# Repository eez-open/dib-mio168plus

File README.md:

### This is a WORK IN PROGRESS!

---

### Ownership and License
The contributors are listed in CONTRIB.TXT. 

Licenses | OSHWA UID
--|--
 | 

### Overview

_Fig 1: MIO168+ without AFE module_

_Fig 2: MIO168+ with AFE3+ installed_

The MIO168+ module features multiple digital I/O, analog outputs and expansion connectors for carry various AFEs.

### Feature list

* On-board [STM32F446ZCT6](https://www.st.com/content/st_com/en/products/microcontrollers-microprocessors/stm32-32-bit-arm-cortex-mcus/stm32-high-performance-mcus/stm32f4-series/stm32f446/stm32f446zc.html) high-performance foundation line MCU, ARM Cortex-M4 with DSP and FPU, 256 KiB Flash, LQFP-144 package 
* AFE interface
* 8 x protected digital inputs (3.3/5/24 V), 2 x fast/slow, 6 x slow
* 8 x digital outputs with multiple protections, voltage clamp 24V, nom. current 330 mA (limit 2.3 A)
* 2 x PWM outputs (protected) or sensor bias power (+/-15 V, max. 10 mA)
* 2 x analog bipolar outputs (+/-5 V, +/-10 V, 0-5 V, 0-10 V). Voltage or current output with protection. 12-bit DAC, replaceable with pin compatible 14- or 16-bit version
* 2 x analog bipolar outputs +/-10 V. 12-bit DAC, replaceable with pin compatible 14- or 16-bit version
* On-board isolated power supply with +/-5.3 V outputs (with 4x multipliers), +/-15 V and +3.3 V LDO
* On-board SDRAM for measured data buffering (optional)
* USB HS PHY
* Firmware download via SPI or USB
* Optional SWD for debugging
* I2C EEPROM for storing board specific parameters
* Dimensions: 180 x 95 mm, 4-layer PCB

### Related topics and links

* [EEZ BB3+](https://github.com/eez-open/eez-bb3plus)
* [MIO168+ AFE3](https://github.com/eez-open/dib-mio168plus-afe3)
* [MIO168](https://github.com/eez-open/dib-mio168) for EEZ BB3 (retired)

---

This work is financed by [NLnet](https://nlnet.nl/project/BB3-CM5/) foundation

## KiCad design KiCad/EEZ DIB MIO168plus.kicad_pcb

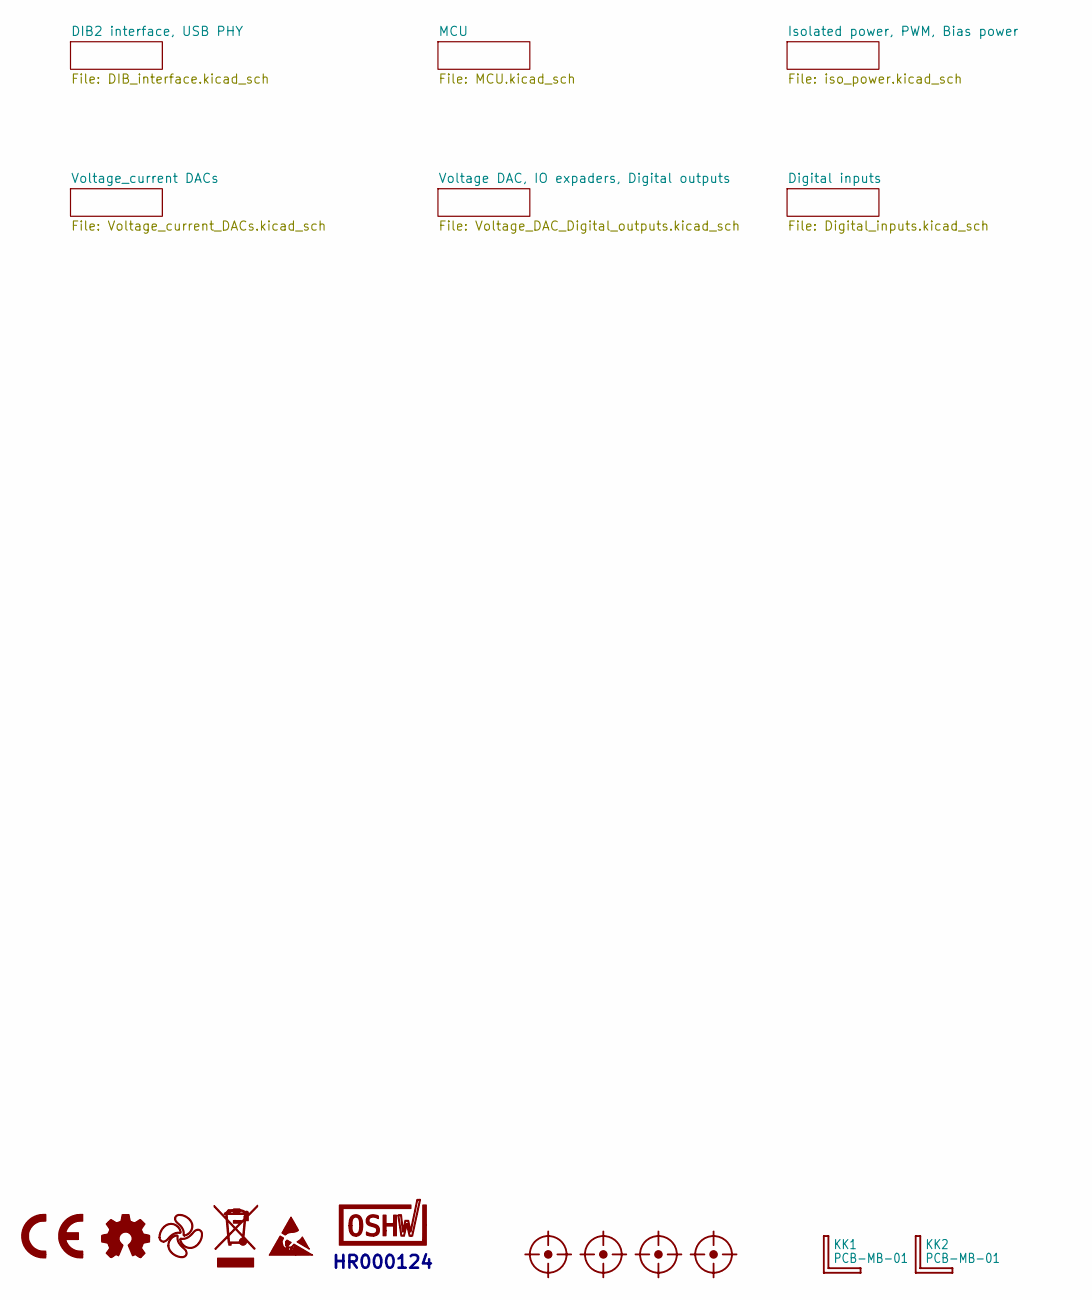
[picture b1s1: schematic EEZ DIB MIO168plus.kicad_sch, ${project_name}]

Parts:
FM1, FM2, FM3, FM4: FIDUCIAL_2; Fiducial_0.75mm_Mask1.5mm
KK1, KK2: PCB-MB-01; DigiKey RPC1760-ND
LOGO1: CE logo
LOGO2: Open hardware logo; Open HW logo
LOGO3: EEZ logo; EEZ logo (outline 6mm)
LOGO4: WEEE logo
LOGO5: ESD logo
LOGO6: OSHWA logo; OSHWA logo 6.6mm

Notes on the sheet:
HR000124

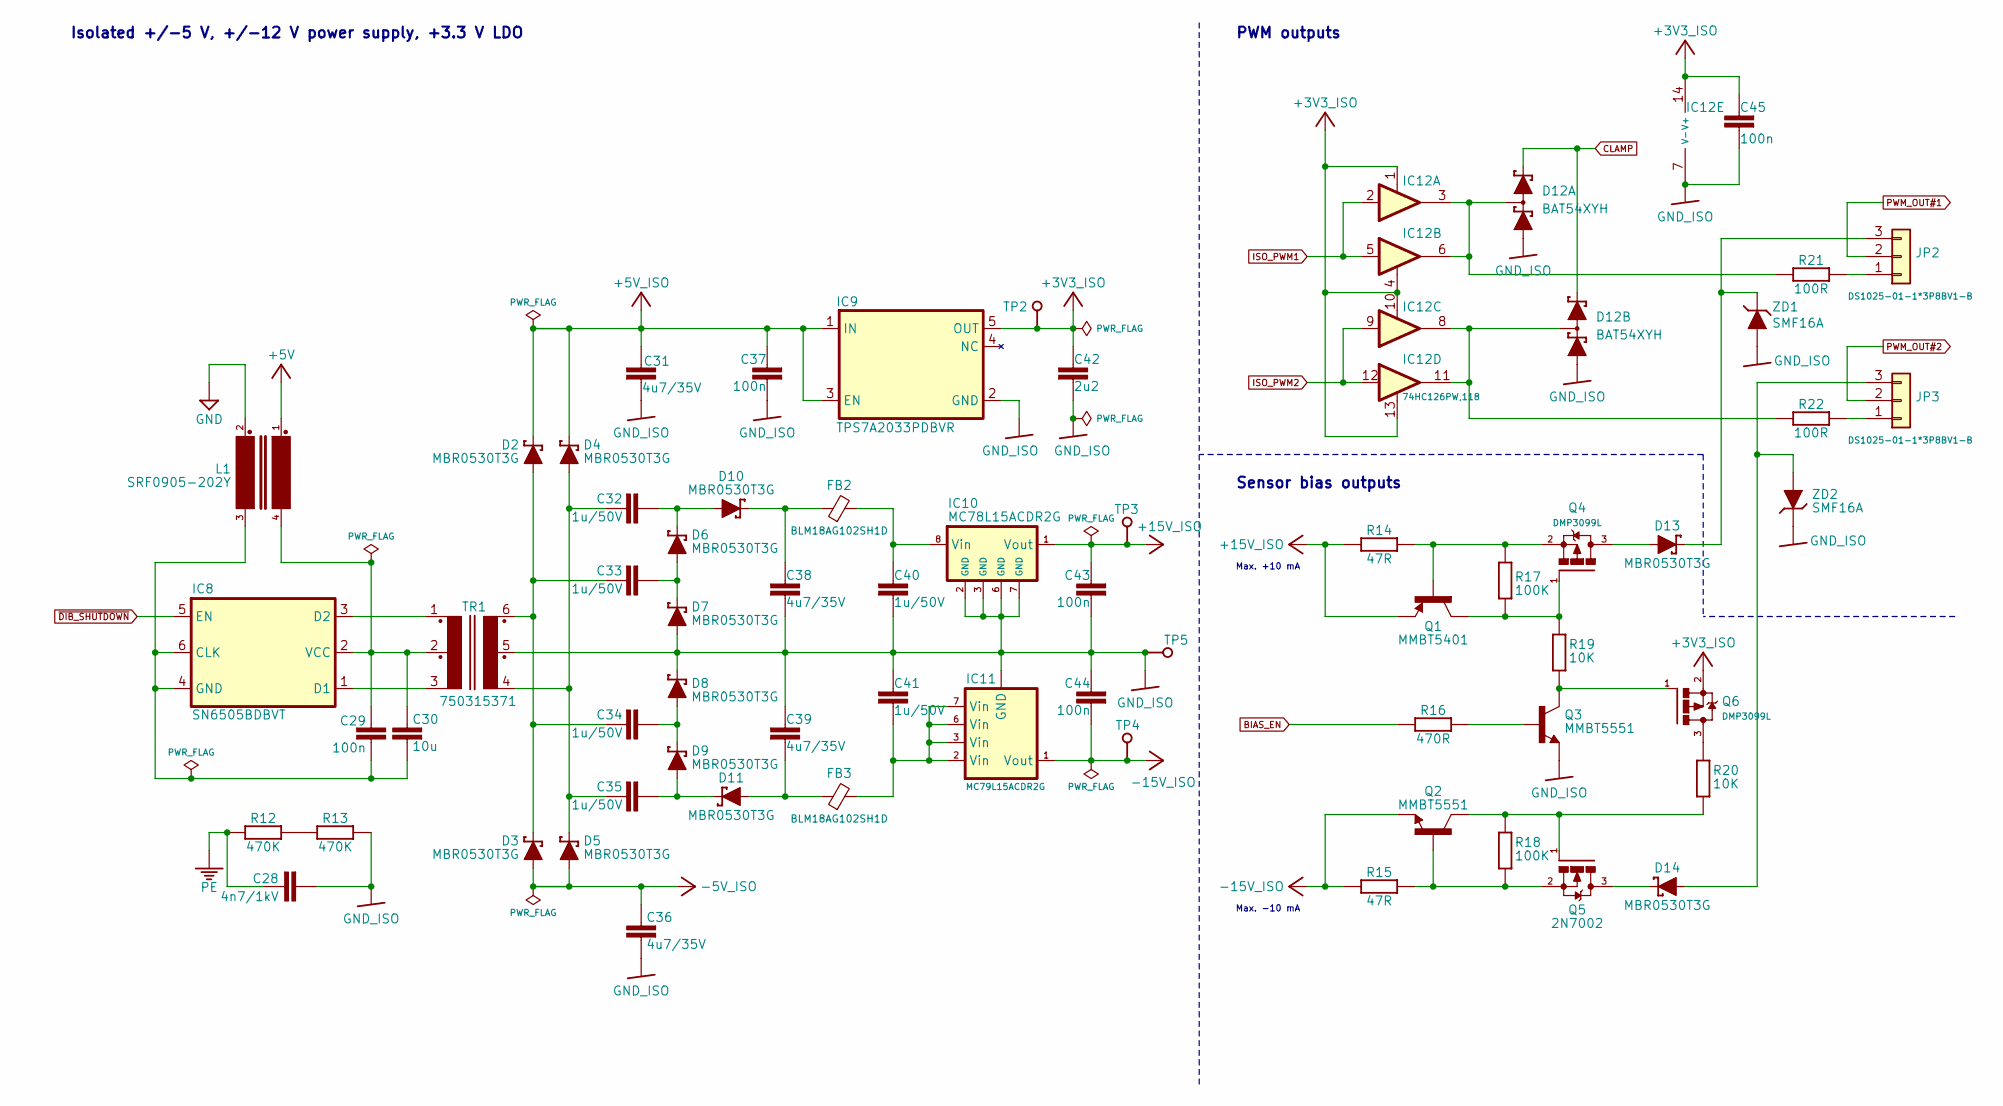
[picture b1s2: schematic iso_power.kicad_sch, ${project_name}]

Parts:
C28: 4n7/1kV; C_1206_3216Metric; DigiKey 732-12074-2-ND
C29, C37, C43, C44, C45: 100n; C_0603_1608Metric; DigiKey 490-4774-1-ND
C30: 10u; C_0805_2012Metric; DigiKey 490-5523-1-ND
C31, C36, C38, C39: 4u7/35V; C_0603_1608Metric; DigiKey 1276-6794-1-ND
C32, C33, C34, C35, C40, C41: 1u/50V; C_0603_1608Metric; DigiKey 1276-1860-1-ND
C42: 2u2; C_0603_1608Metric; DigiKey 490-12738-1-ND
D2, D3, D4, D5, D6, D7, D8, D9, D10, D11, D13, D14: MBR0530T3G; SOD123; DigiKey 863-MBR0530T3G
D12: BAT54XYH; SOP65P210X110-6N; DigiKey 1727-2723-1-ND
FB2, FB3: BLM18AG102SH1D; BEAD0603; DigiKey 490-7809-1-ND
IC8: SN6505BDBVT; DBV0006A_N; DigiKey 296-43154-2-ND
IC9: TPS7A2033PDBVR; DBV5; DigiKey 296-TPS7A2033PDBVRCT-ND
IC10: MC78L15ACDR2G; SOIC127P600X173-8N; DigiKey MC78L15ACDR2GOSDKR-ND
IC11: MC79L15ACDR2G; SOIC127P600X173-8N; DigiKey MC79L15ABDR2GOSDKR
IC12: 74HC126PW,118; PW(R-PDSO-G14); DigiKey 1727-6579-1-ND
JP2, JP3: DS1025-01-1*3P8BV1-B; ZL303-03P; DigiKey 952-1312-ND
L1: SRF0905-202Y; SRF0905; DigiKey SRF0905-202YCT-ND
Q1: MMBT5401; SOT23-BEC; DigiKey MMBT5401-FDICT-ND
Q2, Q3: MMBT5551; SOT23-BEC; DigiKey MMBT5551LT1GOSCT-ND
Q4, Q6: DMP3099L; SOT103P240X110-3N; DigiKey DMP3099L-13DICT-ND
Q5: 2N7002; SOT103P240X110-3N; DigiKey 2N7002LT1GOSCT-ND
R12, R13: 470K; R_0805_2012Metric; DigiKey A126370CT-ND
R14, R15: 47R; R_0603_1608Metric; DigiKey 13-RC0603FR-1347RLCT-ND
R16: 470R; R_0603_1608Metric; DigiKey 13-AC0603FR-7W470RLCT-ND
R17, R18: 100K; R_0603_1608Metric; DigiKey 311-100KHRCT-ND
R19, R20: 10K; R_0603_1608Metric; DigiKey 1712-CRGH0603F10KCT-ND
R21, R22: 100R; R_0603_1608Metric; DigiKey 13-RC0603FR-10100RLCT-ND
TP2, TP3, TP4: Test; Testhole 24_50mils
TP5: Test; TEST-5
TR1: 750315371; MURATA_78615; DigiKey 1297-1178-1-ND
ZD1, ZD2: SMF16A; SODFL3718X130N; DigiKey 4878-SMF16ATR-ND

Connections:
+3V3_ISO: C42.1, C45.2, IC9.5 (OUT), IC12.1 (EN), IC12.4 (EN), IC12.10 (EN), IC12.13 (EN), IC12.14 (V+), Q6.2 (S), TP2.1 (P$1_1); also elsewhere on the board
+5V: L1.1; also elsewhere on the board
+5V_ISO: C31.2, C37.1, D2.C, D4.C, IC9.1 (IN), IC9.3 (EN); also elsewhere on the board
+15V_ISO: C43.1, IC10.1 (Vout), Q1.E, R14.1, TP3.1 (P$1_1); also elsewhere on the board
-5V_ISO: C36.2, D3.A, D5.A; also elsewhere on the board
-15V_ISO: C44.2, IC11.1 (Vout), Q2.E, R15.1, TP4.1 (P$1_1); also elsewhere on the board
BIAS_EN: R16.2; also elsewhere on the board
CLAMP: D12.2 (K2), D12.5 (K3); also elsewhere on the board
GND: L1.2; also elsewhere on the board
GND_ISO: C28.2, C31.1, C36.1, C37.2, C38.2, C39.1, C40.1, C41.2, C42.2, C43.2, C44.1, C45.1, D7.A, D8.C, D12.1 (A1), D12.4 (A4), IC9.2 (GND), IC10.2 (GND), IC10.3 (GND), IC10.6 (GND), IC10.7 (GND), IC11.5 (GND), IC12.7 (V-), Q3.E, R13.2, TP5.1 (P$1_1), TR1.5, ZD1.C, ZD2.A; also elsewhere on the board
ISO_PWM1: IC12.2 (I), IC12.5 (I); also elsewhere on the board
ISO_PWM2: IC12.9 (I), IC12.12 (I); also elsewhere on the board
unnamed: C32.1, D6.C, D10.A
unnamed: C32.2, C35.2, D4.A, D5.C, TR1.4
unnamed: C33.1, D6.A, D7.C
unnamed: C33.2, C34.2, D2.A, D3.C, TR1.6
unnamed: C34.1, D8.A, D9.C
unnamed: C35.1, D9.A, D11.C
unnamed: C38.1, D10.C, FB2.1
unnamed: C39.2, D11.A, FB3.1
unnamed: C41.1, FB3.2, IC11.2 (Vin), IC11.3 (Vin), IC11.6 (Vin), IC11.7 (Vin)
unnamed: D12.6 (K1A2), IC12.3 (O), IC12.6 (O), R21.2
unnamed: D12.3 (A3K4), IC12.8 (O), IC12.11 (O), R22.2
unnamed: C29.2, C30.1, IC8.4 (GND), IC8.6 (CLK), L1.3
unnamed: IC8.1 (D1), TR1.3
unnamed: IC8.3 (D2), TR1.1
unnamed: C29.1, C30.2, IC8.2 (VCC), L1.4, TR1.2
unnamed: C40.2, FB2.2, IC10.8 (Vin)
unnamed: JP2.1, R21.1
unnamed: D13.C, JP2.3, ZD1.A
unnamed: JP3.1, R22.1
unnamed: D14.A, JP3.3, ZD2.C
unnamed: Q3.B, R16.1
unnamed: D13.A, Q4.3 (D)
unnamed: Q1.C, Q4.1 (G), R17.2, R19.1
unnamed: Q1.B, Q4.2 (S), R14.2, R17.1
unnamed: D14.C, Q5.3 (D)
unnamed: Q2.C, Q5.1 (G), R18.1, R20.2
unnamed: Q2.B, Q5.2 (S), R15.2, R18.2
unnamed: Q6.3 (D), R20.1
unnamed: Q3.C, Q6.1 (G), R19.2
unnamed: R12.2, R13.1
PE: C28.1, R12.1; also elsewhere on the board
PWM_OUT#1: JP2.2; also elsewhere on the board
PWM_OUT#2: JP3.2; also elsewhere on the board
~DIB_SHUTDOWN: IC8.5 (EN); also elsewhere on the board

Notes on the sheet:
Max. -10 mA
Max. +10 mA
Sensor bias outputs
PWM outputs
Isolated +/-5 V, +/-12 V power supply, +3.3 V LDO

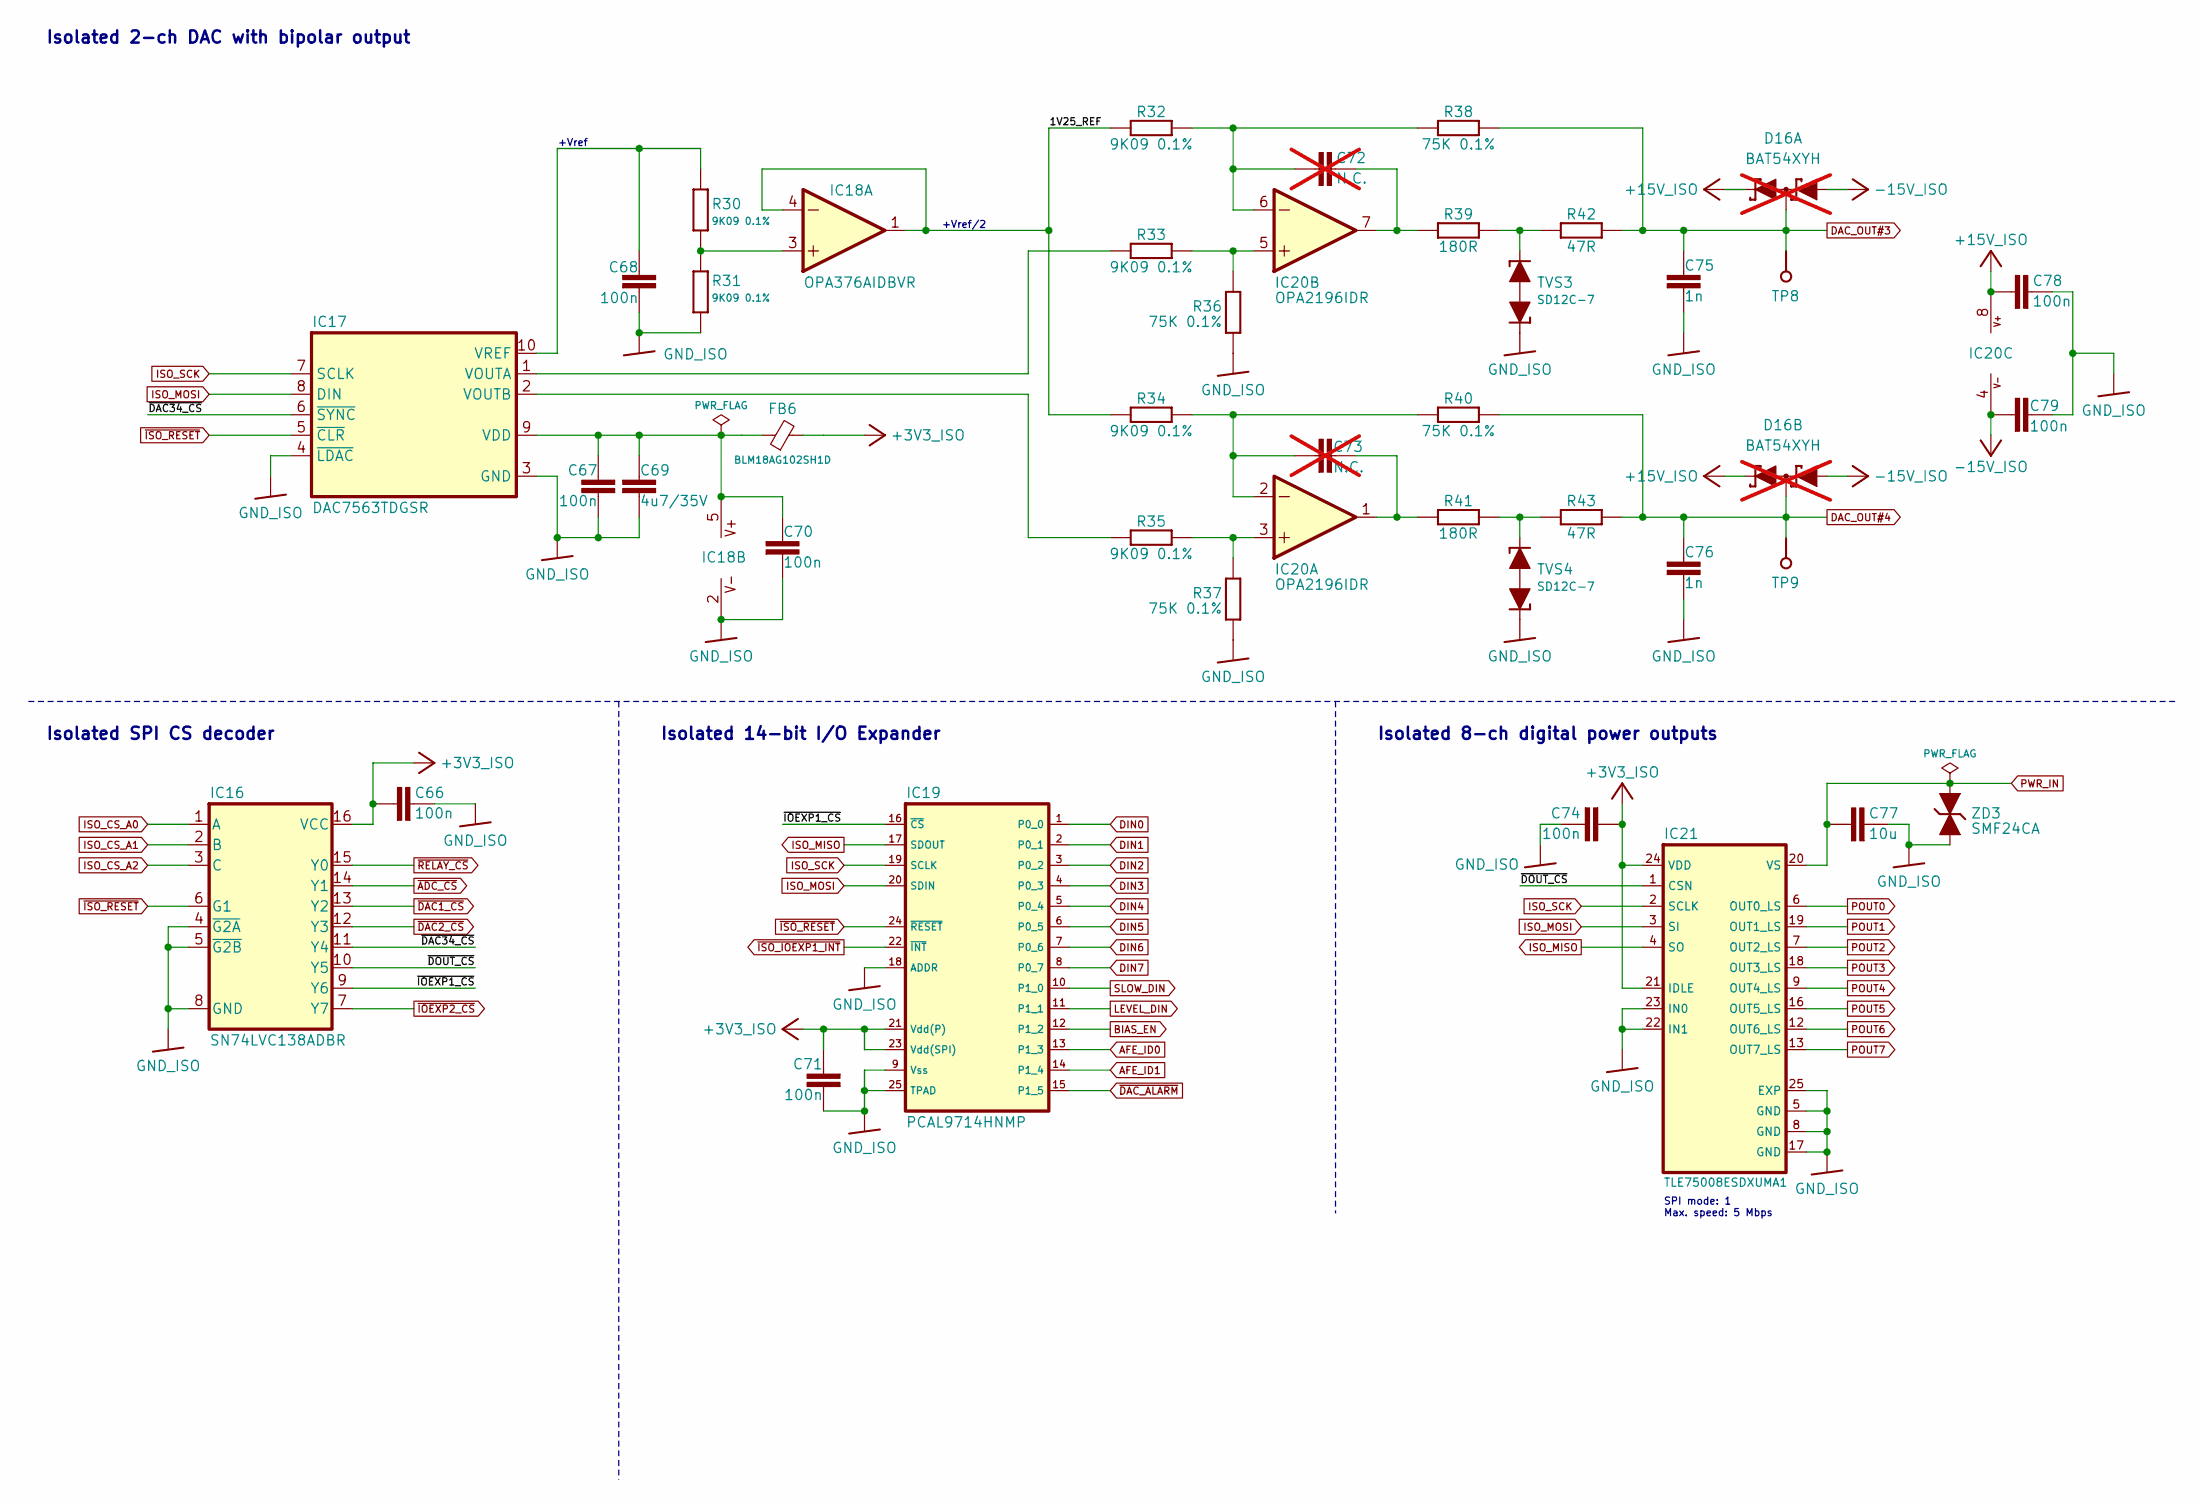
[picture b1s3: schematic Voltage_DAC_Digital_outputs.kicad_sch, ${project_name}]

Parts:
C66, C67, C68, C70, C71, C74, C78, C79: 100n; C_0603_1608Metric; DigiKey 490-4774-1-ND
C69: 4u7/35V; C_0603_1608Metric; DigiKey 1276-6794-1-ND
C72, C73: N.C.; C_0603_1608Metric; not fitted
C75, C76: 1n; C_0603_1608Metric; DigiKey 1276-1018-2-ND
C77: 10u; C_0805_2012Metric; DigiKey 490-5523-1-ND
D16: BAT54XYH; SOP65P210X110-6N; DigiKey 1727-2723-1-ND; not fitted
FB6: BLM18AG102SH1D; BEAD0603; DigiKey 490-7809-1-ND
IC16: SN74LVC138ADBR; DB16; DigiKey 296-8460-1-ND
IC17: DAC7563TDGSR; DGS10; DigiKey 296-43287-1-ND
IC18: OPA376AIDBVR; SOT23-5L_STM; DigiKey 296-39130-2-ND
IC19: PCAL9714HNMP; QFN50P400X400X100-25N; DigiKey 568-PCAL9714HNMPCT-ND
IC20: OPA2196IDR; SOIC127P600X173-8N; DigiKey 296-48159-1-ND
IC21: TLE75008ESDXUMA1; SOP65P600X115-25N; DigiKey 448-TLE75008ESDXUMA1CT-ND
R30, R31, R32, R33, R34, R35: 9K09 0.1%; R_0603_1608Metric; DigiKey YAG4788CT-ND
R36, R37, R38, R40: 75K 0.1%; R_0603_1608Metric; DigiKey YAG1730CT-ND
R39, R41: 180R; R_0603_1608Metric; DigiKey 13-RC0603FR-13180RLCT-ND
R42, R43: 47R; R_0603_1608Metric; DigiKey 13-RC0603FR-1347RLCT-ND
TP8, TP9: Test; Testhole 24_50mils
TVS3, TVS4: SD12C-7; SOD-323_PESD; DigiKey 31-SD12C-7CT-ND
ZD3: SMF24CA; SODFL3718X130N; DigiKey 4878-SMF24CADKR-ND

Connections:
+3V3_ISO: C66.1, C71.1, C74.2, FB6.2, IC16.16 (VCC), IC19.21 (Vdd(P)), IC19.23 (Vdd(SPI)), IC21.21 (IDLE), IC21.24 (VDD); also elsewhere on the board
+15V_ISO: C78.1, D16.2 (K2), D16.5 (K3), IC20.8 (V+); also elsewhere on the board
-15V_ISO: C79.1, D16.1 (A1), D16.4 (A4), IC20.4 (V-); also elsewhere on the board
/Voltage DAC, IO expaders, Digital outputs/1V25_REF: IC18.1 (OUT), IC18.4 (-IN), R32.2, R34.2
/Voltage DAC, IO expaders, Digital outputs/~DAC34_CS: IC16.11 (Y4), IC17.6 (~SYNC)
/Voltage DAC, IO expaders, Digital outputs/~DOUT_CS: IC16.10 (Y5), IC21.1 (CSN)
/Voltage DAC, IO expaders, Digital outputs/~IOEXP1_CS: IC16.9 (Y6), IC19.16 (~CS)
AFE_ID0: IC19.13 (P1_3); also elsewhere on the board
AFE_ID1: IC19.14 (P1_4); also elsewhere on the board
BIAS_EN: IC19.12 (P1_2); also elsewhere on the board
DAC_OUT#3: C75.1, D16.6 (K1A2), R38.1, R42.2, TP8.1 (P$1_1); also elsewhere on the board
DAC_OUT#4: C76.1, D16.3 (A3K4), R40.1, R43.2, TP9.1 (P$1_1); also elsewhere on the board
DIN0: IC19.1 (P0_0); also elsewhere on the board
DIN1: IC19.2 (P0_1); also elsewhere on the board
DIN2: IC19.3 (P0_2); also elsewhere on the board
DIN3: IC19.4 (P0_3); also elsewhere on the board
DIN4: IC19.5 (P0_4); also elsewhere on the board
DIN5: IC19.6 (P0_5); also elsewhere on the board
DIN6: IC19.7 (P0_6); also elsewhere on the board
DIN7: IC19.8 (P0_7); also elsewhere on the board
GND_ISO: C66.2, C67.2, C68.1, C69.1, C70.2, C71.2, C74.1, C75.2, C76.2, C77.1, C78.2, C79.2, IC16.4 (~G2A), IC16.5 (~G2B), IC16.8 (GND), IC17.3 (GND), IC17.4 (~LDAC), IC18.2 (V-), IC19.9 (Vss), IC19.18 (ADDR), IC19.25 (TPAD), IC21.5 (GND), IC21.8 (GND), IC21.17 (GND), IC21.22 (IN1), IC21.23 (IN0), IC21.25 (EXP), R31.2, R36.2, R37.2, TVS3.C1 (1), TVS4.C1 (1), ZD3.C; also elsewhere on the board
ISO_CS_A0: IC16.1 (A); also elsewhere on the board
ISO_CS_A1: IC16.2 (B); also elsewhere on the board
ISO_CS_A2: IC16.3 (C); also elsewhere on the board
ISO_MISO: IC19.17 (SDOUT), IC21.4 (SO); also elsewhere on the board
ISO_MOSI: IC17.8 (DIN), IC19.20 (SDIN), IC21.3 (SI); also elsewhere on the board
ISO_SCK: IC17.7 (SCLK), IC19.19 (SCLK), IC21.2 (SCLK); also elsewhere on the board
LEVEL_DIN: IC19.11 (P1_1); also elsewhere on the board
unnamed: C67.1, C69.2, C70.1, FB6.1, IC17.9 (VDD), IC18.5 (V+)
unnamed: IC17.1 (VOUTA), R33.2
unnamed: IC17.2 (VOUTB), R35.2
unnamed: C68.2, IC17.10 (VREF), R30.1
unnamed: IC18.3 (+IN), R30.2, R31.1
unnamed: IC20.3 (+IN), R35.1, R37.1
unnamed: C73.1, IC20.2 (-IN), R34.1, R40.2
unnamed: C73.2, IC20.1 (OUT), R41.1
unnamed: IC20.5 (+IN), R33.1, R36.1
unnamed: C72.1, IC20.6 (-IN), R32.1, R38.2
unnamed: C72.2, IC20.7 (OUT), R39.1
unnamed: R39.2, R42.1, TVS3.C2 (2)
unnamed: R41.2, R43.1, TVS4.C2 (2)
POUT0: IC21.6 (OUT0_LS); also elsewhere on the board
POUT1: IC21.19 (OUT1_LS); also elsewhere on the board
POUT2: IC21.7 (OUT2_LS); also elsewhere on the board
POUT3: IC21.18 (OUT3_LS); also elsewhere on the board
POUT4: IC21.9 (OUT4_LS); also elsewhere on the board
POUT5: IC21.16 (OUT5_LS); also elsewhere on the board
POUT6: IC21.12 (OUT6_LS); also elsewhere on the board
POUT7: IC21.13 (OUT7_LS); also elsewhere on the board
PWR_IN: C77.2, IC21.20 (VS), ZD3.A; also elsewhere on the board
SLOW_DIN: IC19.10 (P1_0); also elsewhere on the board
~ADC_CS: IC16.14 (Y1); also elsewhere on the board
~DAC1_CS: IC16.13 (Y2); also elsewhere on the board
~DAC2_CS: IC16.12 (Y3); also elsewhere on the board
~DAC_ALARM: IC19.15 (P1_5); also elsewhere on the board
~IOEXP2_CS: IC16.7 (Y7); also elsewhere on the board
~ISO_IOEXP1_INT: IC19.22 (~INT); also elsewhere on the board
~ISO_RESET: IC16.6 (G1), IC17.5 (~CLR), IC19.24 (~RESET); also elsewhere on the board
~RELAY_CS: IC16.15 (Y0); also elsewhere on the board

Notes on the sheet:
SPI mode: 1 Max. speed: 5 Mbps
+Vref
Isolated SPI CS decoder
+Vref/2
Isolated 8-ch digital power outputs
Isolated 2-ch DAC with bipolar output
Isolated 14-bit I/O Expander

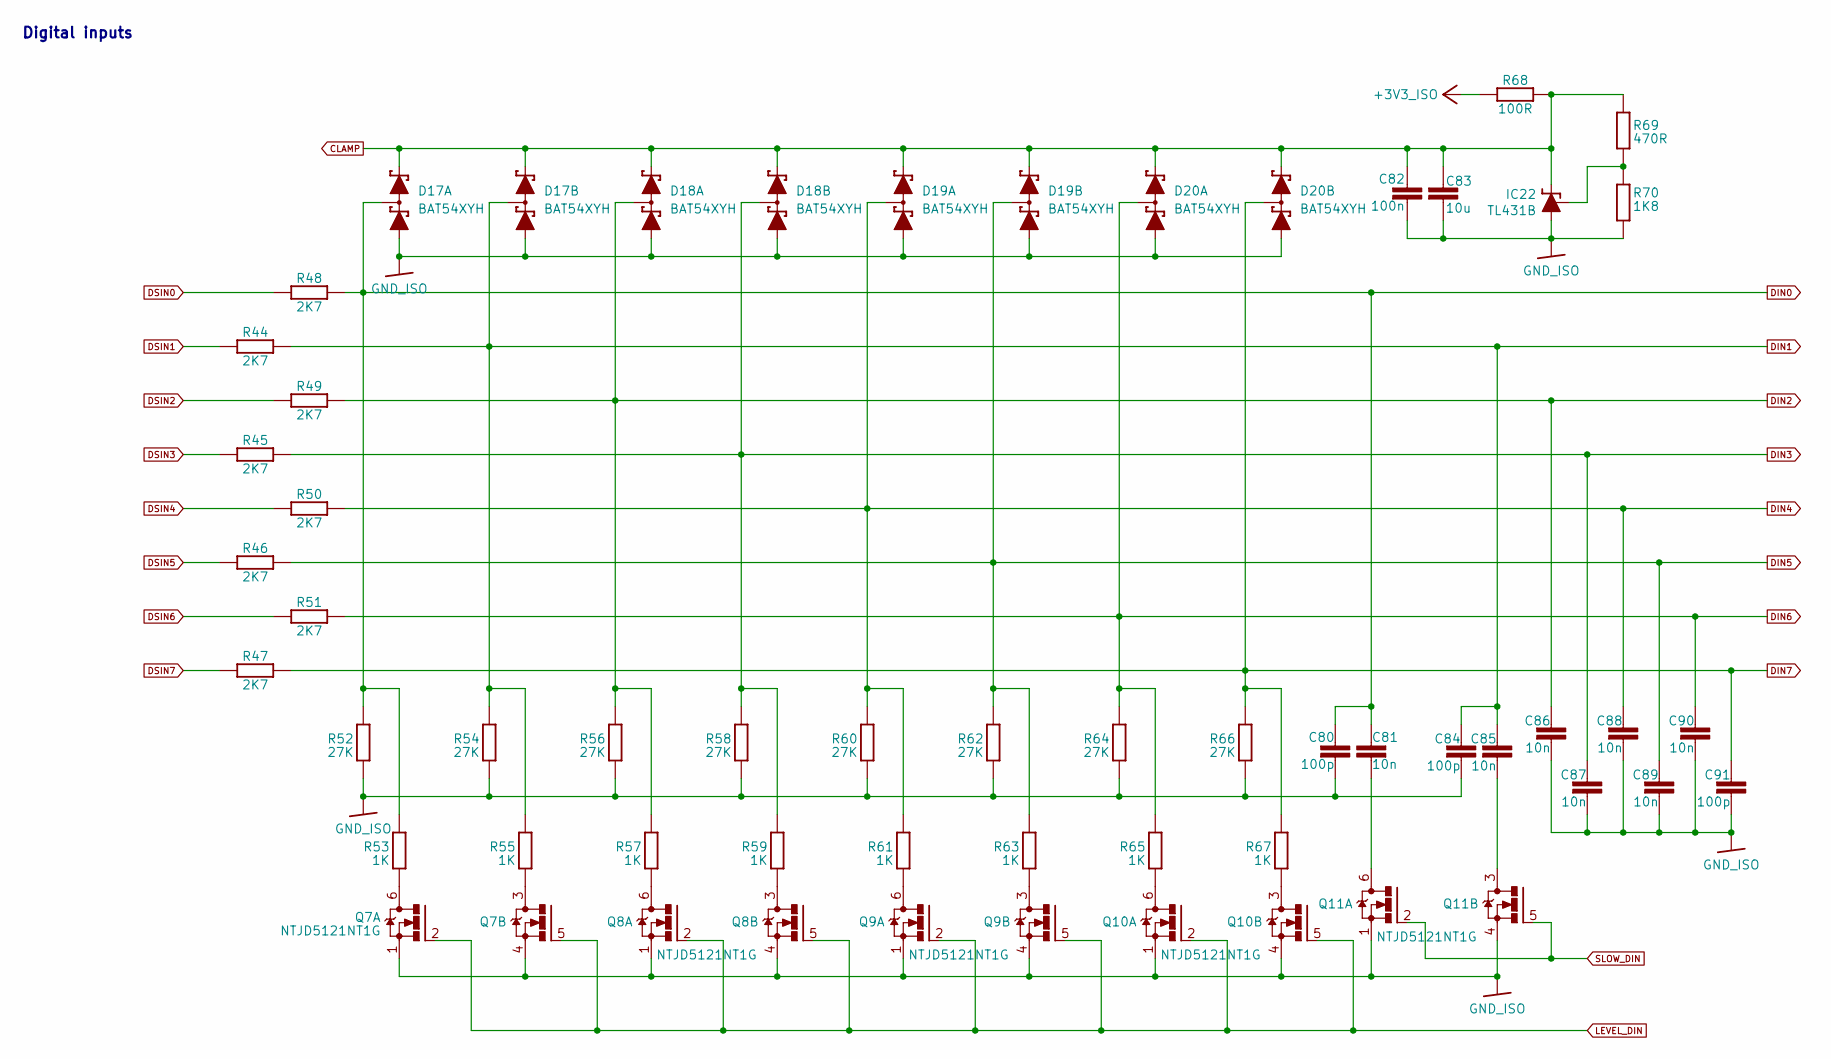
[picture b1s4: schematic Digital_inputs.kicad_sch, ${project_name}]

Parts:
C80, C84, C91: 100p; C_0603_1608Metric; DigiKey 490-11153-1-ND
C81, C85, C86, C87, C88, C89, C90: 10n; C_0603_1608Metric; DigiKey 1276-1009-1-ND
C82: 100n; C_0603_1608Metric; DigiKey 490-4774-1-ND
C83: 10u; C_0805_2012Metric; DigiKey 490-5523-1-ND
D17, D18, D19, D20: BAT54XYH; SOP65P210X110-6N; DigiKey 1727-2723-1-ND
IC22: TL431B; SOT103P240X110-3N; DigiKey 296-17332-1-ND
Q7, Q8, Q9, Q10, Q11: NTJD5121NT1G; SC88; DigiKey NTJD5121NT1GOSCT-ND
R44, R45, R46, R47, R48, R49, R50, R51: 2K7; R_1206_3216Metric; DigiKey 311-2.70KFRCT-ND
R52, R54, R56, R58, R60, R62, R64, R66: 27K; R_0603_1608Metric; DigiKey 311-27.0KHRCT-ND
R53, R55, R57, R59, R61, R63, R65, R67: 1K; R_0603_1608Metric; DigiKey 13-RC0603FR-131KLCT-ND
R68: 100R; R_0603_1608Metric; DigiKey 13-RC0603FR-10100RLCT-ND
R69: 470R; R_0603_1608Metric; DigiKey 13-AC0603FR-7W470RLCT-ND
R70: 1K8; R_0603_1608Metric; DigiKey 13-RC0603FR-131K8LCT-ND

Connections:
+3V3_ISO: R68.1; also elsewhere on the board
CLAMP: C82.1, C83.1, D17.2 (K2), D17.5 (K3), D18.2 (K2), D18.5 (K3), D19.2 (K2), D19.5 (K3), D20.2 (K2), D20.5 (K3), IC22.1 (C), R68.2, R69.1; also elsewhere on the board
DIN0: C80.1, C81.1, D17.6 (K1A2), R48.2, R52.2, R53.1; also elsewhere on the board
DIN1: C84.1, C85.1, D17.3 (A3K4), R44.2, R54.2, R55.1; also elsewhere on the board
DIN2: C86.1, D18.6 (K1A2), R49.2, R56.2, R57.1; also elsewhere on the board
DIN3: C87.1, D18.3 (A3K4), R45.2, R58.2, R59.1; also elsewhere on the board
DIN4: C88.1, D19.6 (K1A2), R50.2, R60.2, R61.1; also elsewhere on the board
DIN5: C89.1, D19.3 (A3K4), R46.2, R62.2, R63.1; also elsewhere on the board
DIN6: C90.1, D20.6 (K1A2), R51.2, R64.2, R65.1; also elsewhere on the board
DIN7: C91.1, D20.3 (A3K4), R47.2, R66.2, R67.1; also elsewhere on the board
DSIN0: R48.1; also elsewhere on the board
DSIN1: R44.1; also elsewhere on the board
DSIN2: R49.1; also elsewhere on the board
DSIN3: R45.1; also elsewhere on the board
DSIN4: R50.1; also elsewhere on the board
DSIN5: R46.1; also elsewhere on the board
DSIN6: R51.1; also elsewhere on the board
DSIN7: R47.1; also elsewhere on the board
GND_ISO: C80.2, C82.2, C83.2, C84.2, C86.2, C87.2, C88.2, C89.2, C90.2, C91.2, D17.1 (A1), D17.4 (A4), D18.1 (A1), D18.4 (A4), D19.1 (A1), D19.4 (A4), D20.1 (A1), D20.4 (A4), IC22.3 (A), Q7.1 (S), Q7.4 (S), Q8.1 (S), Q8.4 (S), Q9.1 (S), Q9.4 (S), Q10.1 (S), Q10.4 (S), Q11.1 (S), Q11.4 (S), R52.1, R54.1, R56.1, R58.1, R60.1, R62.1, R64.1, R66.1, R70.2; also elsewhere on the board
LEVEL_DIN: Q7.2 (G), Q7.5 (G), Q8.2 (G), Q8.5 (G), Q9.2 (G), Q9.5 (G), Q10.2 (G), Q10.5 (G); also elsewhere on the board
unnamed: IC22.2 (R), R69.2, R70.1
unnamed: Q7.6 (D), R53.2
unnamed: Q7.3 (D), R55.2
unnamed: Q8.6 (D), R57.2
unnamed: Q8.3 (D), R59.2
unnamed: Q9.6 (D), R61.2
unnamed: Q9.3 (D), R63.2
unnamed: Q10.6 (D), R65.2
unnamed: Q10.3 (D), R67.2
unnamed: C81.2, Q11.6 (D)
unnamed: C85.2, Q11.3 (D)
SLOW_DIN: Q11.2 (G), Q11.5 (G); also elsewhere on the board

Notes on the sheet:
Digital inputs

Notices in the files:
parts and their libraries:
project_license: Licensed under the TAPR Open Hardware License (www.tapr.org/OHL)
